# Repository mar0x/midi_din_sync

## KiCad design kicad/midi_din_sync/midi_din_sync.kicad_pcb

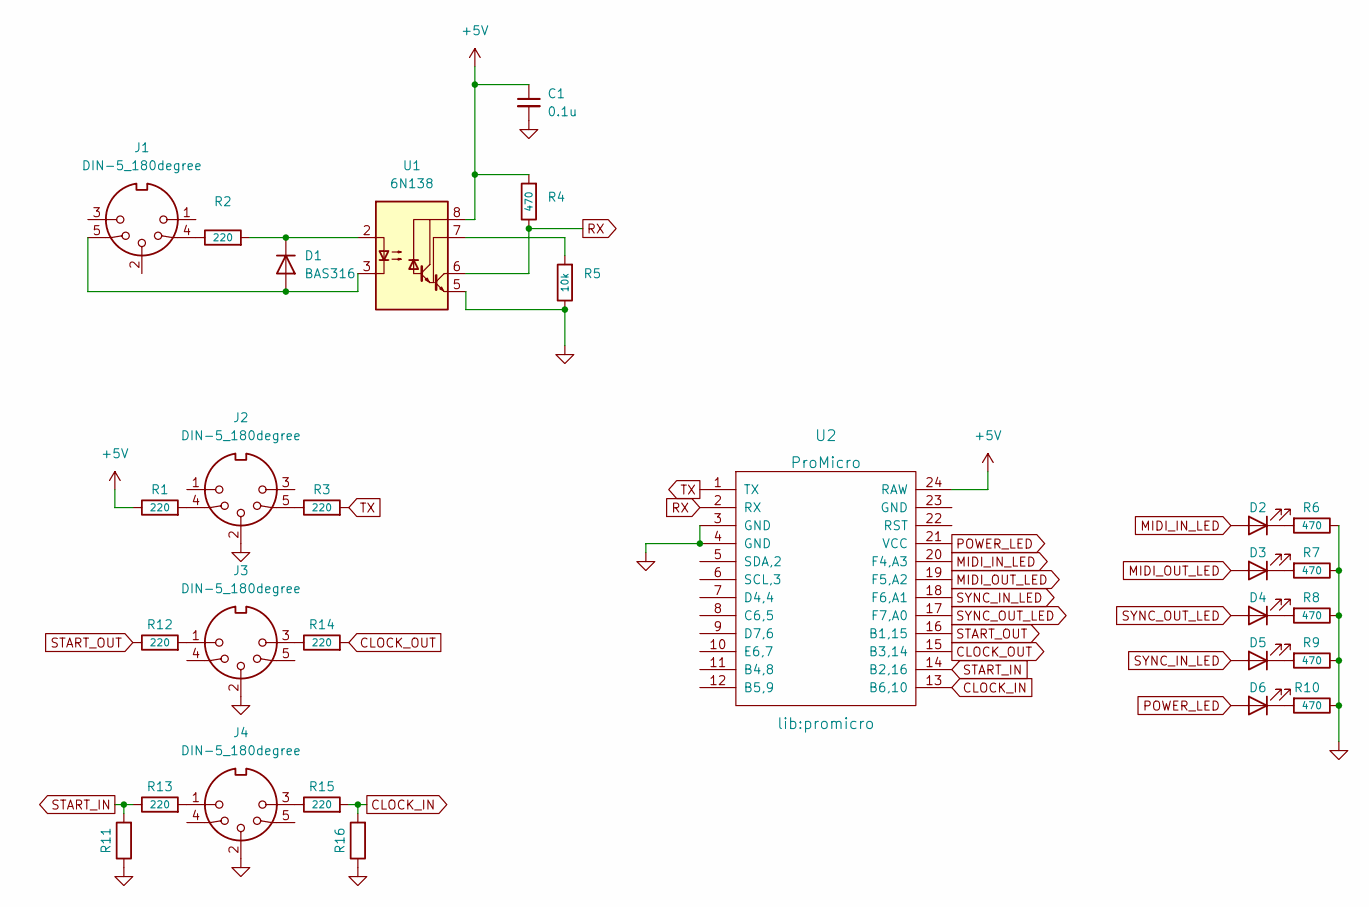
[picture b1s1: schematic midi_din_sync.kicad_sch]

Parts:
C1: 0.1u; C_0805_2012Metric_Pad1.18x1.45mm_HandSolder
D1: BAS316; D_SOD-323
D2, D3, D4, D5, D6: LED; PinSocket_1x02_P2.54mm_Vertical
J1, J2, J3, J4: DIN-5_180degree; DIN5MIDI-OOTDTY
R1, R2, R3, R12, R13, R14, R15: 220; R_0805_2012Metric_Pad1.20x1.40mm_HandSolder
R4, R6, R7, R8, R9, R10: 470; R_0805_2012Metric_Pad1.20x1.40mm_HandSolder
R5: 10k; R_0805_2012Metric_Pad1.20x1.40mm_HandSolder
R11, R16: R_0805_2012Metric_Pad1.20x1.40mm_HandSolder
U1: 6N138; DIP-8_W7.62mm_Socket_LongPads
U2: ProMicro; promicro

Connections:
+5V: C1.1, R1.1, R4.2, U1.8 (VCC), U2.24 (RAW)
CLOCK_IN: R15.2, R16.2, U2.13 (B6,10)
CLOCK_OUT: R14.2, U2.15 (B3,14)
GND: C1.2, J2.2, J3.2, J4.2, R5.1, R6.1, R7.1, R8.1, R9.1, R10.1, R11.1, R16.1, U1.5 (GND), U2.3 (GND), U2.4 (GND)
MIDI_IN_LED: D2.2 (A), U2.20 (F4,A3)
MIDI_OUT_LED: D3.2 (A), U2.19 (F5,A2)
unnamed: D1.1 (K), R2.2, U1.2 (C1)
unnamed: D1.2 (A), J1.5, U1.3 (C2)
unnamed: D2.1 (K), R6.2
unnamed: D3.1 (K), R7.2
unnamed: D4.1 (K), R8.2
unnamed: D5.1 (K), R9.2
unnamed: D6.1 (K), R10.2
unnamed: J1.4, R2.1
unnamed: J2.4, R1.2
unnamed: J2.5, R3.1
unnamed: J3.1, R12.2
unnamed: J3.3, R14.1
unnamed: J4.1, R13.2
unnamed: J4.3, R15.1
unnamed: R5.2, U1.7 (VO1)
POWER_LED: D6.2 (A), U2.21 (VCC)
RX: R4.1, U1.6 (VO2), U2.2 (RX)
START_IN: R11.2, R13.1, U2.14 (B2,16)
START_OUT: R12.1, U2.16 (B1,15)
SYNC_IN_LED: D5.2 (A), U2.18 (F6,A1)
SYNC_OUT_LED: D4.2 (A), U2.17 (F7,A0)
TX: R3.2, U2.1 (TX)

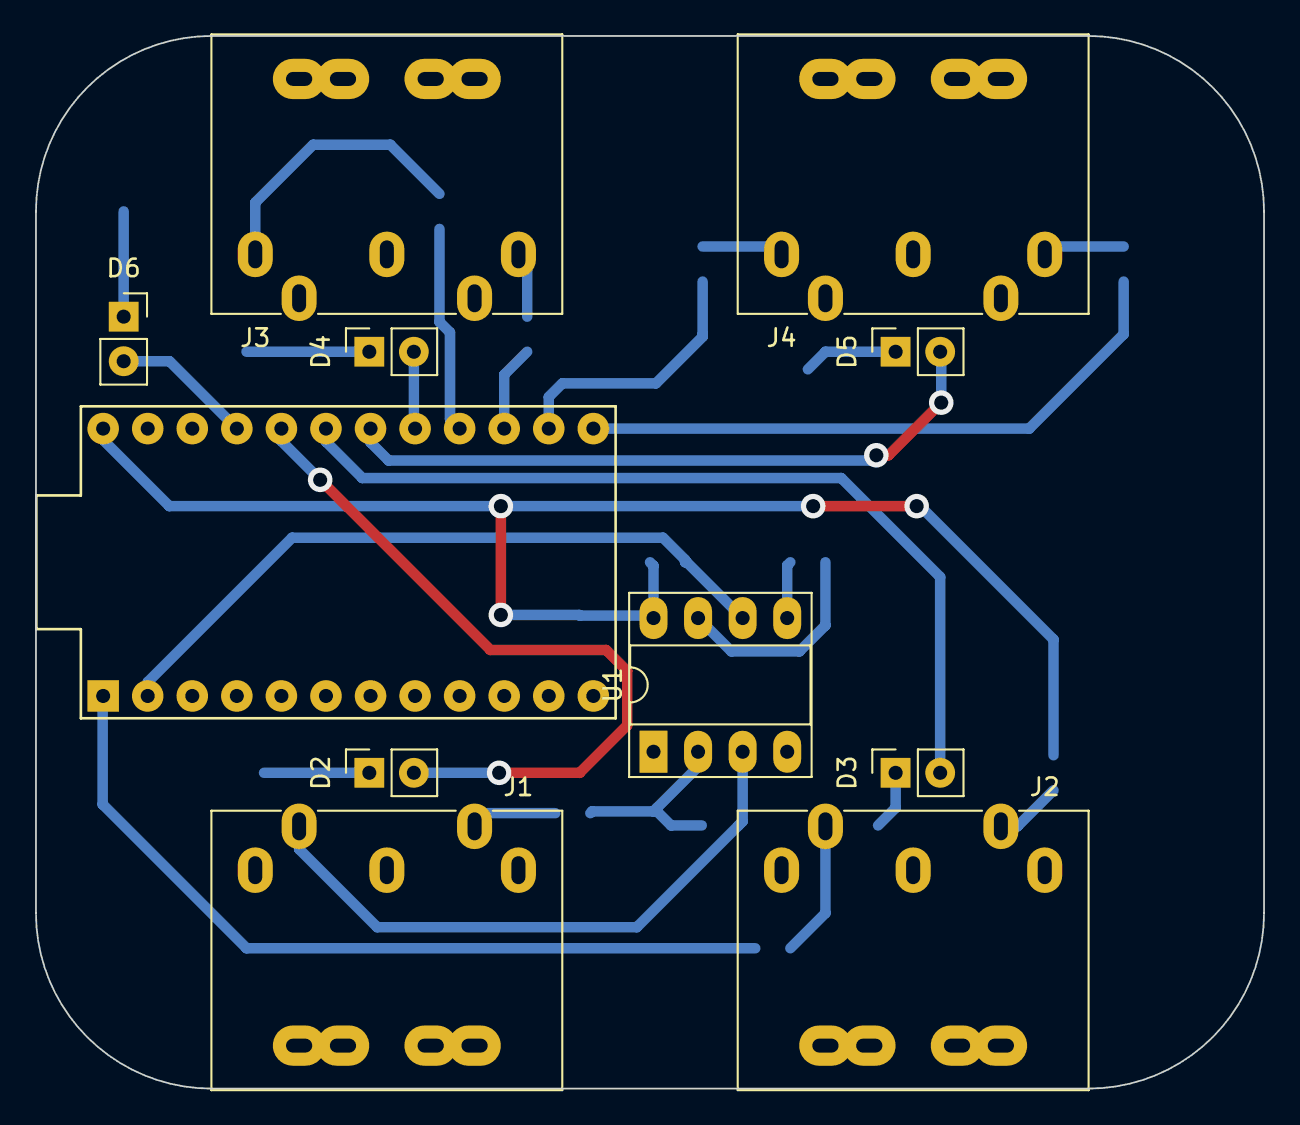
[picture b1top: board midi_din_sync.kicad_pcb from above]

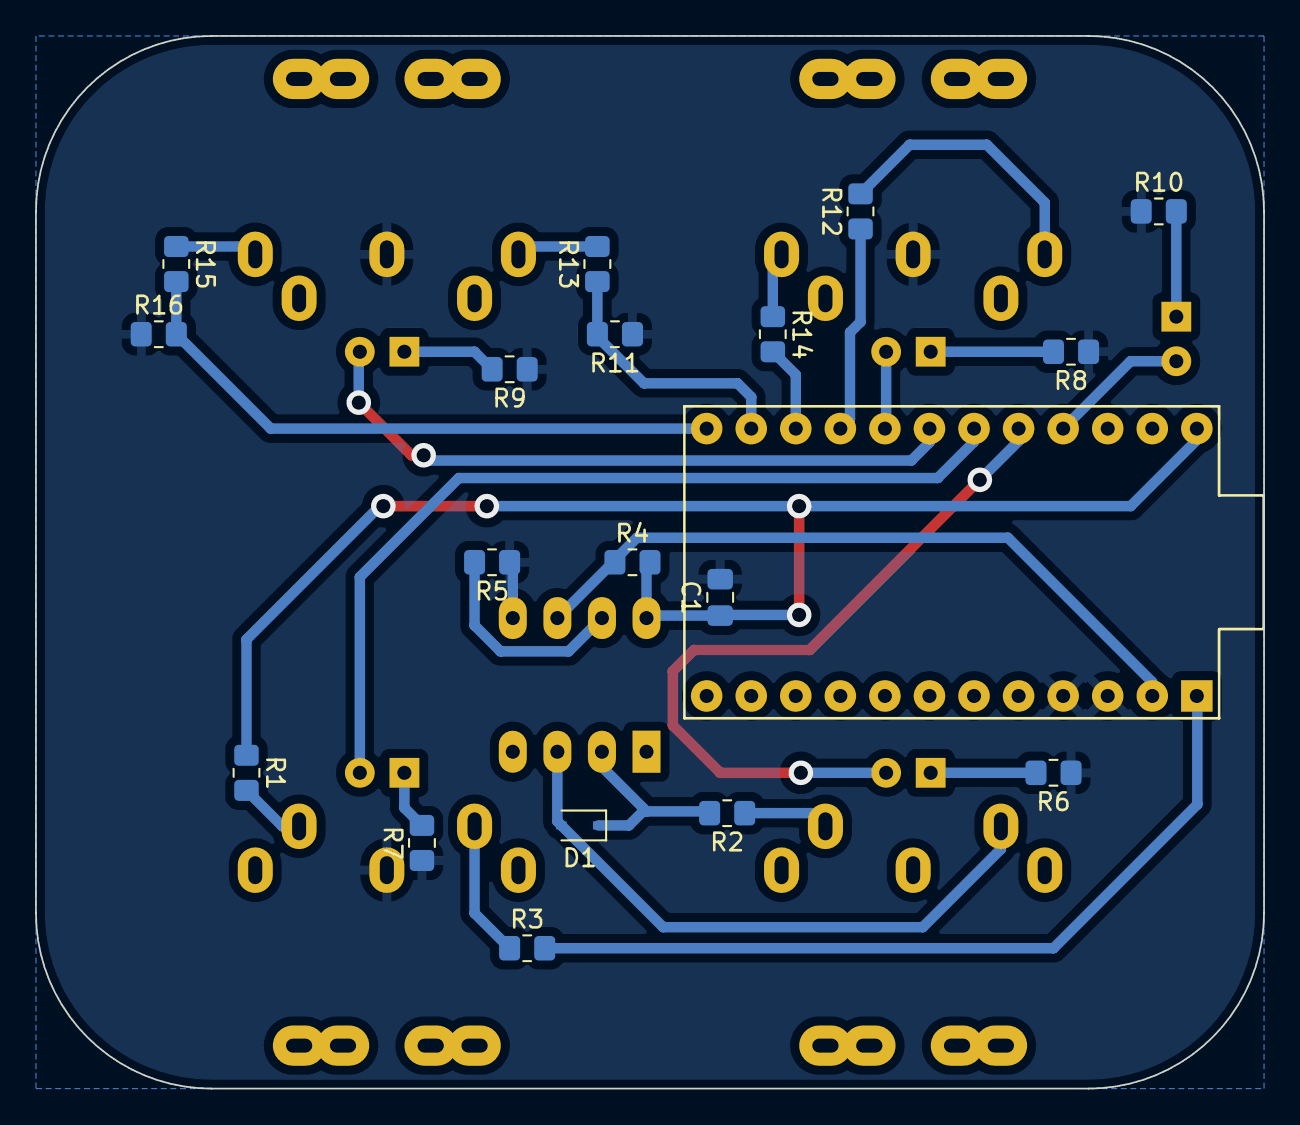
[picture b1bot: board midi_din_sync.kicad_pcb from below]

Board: 2 copper layers, 70.0 x 60.0 mm, 29 parts (18 on the bottom side), 28 nets.

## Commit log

2022-11-22 Working on schematic and PCB
2022-11-26 Minor movements
2022-11-26 Introducing rounded tracks board
